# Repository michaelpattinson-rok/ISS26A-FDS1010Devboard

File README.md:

# FDS1010 Devboard E.1

Rev E.1 is an 85 × 60 mm, two layer, through hole Devboard for one FDS1010 channel. Signal Bench 3.7.11 records the board over USB using the original Raspberry Pi Pico W or Arduino UNO R4 Minima.

| Start here | Contents |
| --- | --- |
| [Assembly and use PDF](Assembly%20and%20Use.pdf) | 77 pages covering components, soldering, orientation, wiring, diagnostics, and bench checks. The software pages document the earlier finite capture workflow. |
| [Pico wiring PNG](Pico%20W%20to%20Devboard%20E.1%20Wiring.png) · [Uno wiring PNG](Arduino%20UNO%20R4%20Minima%20to%20Rev%20E.1%20Wiring.png) | Physical pins and power for both supported Signal Bench hosts. |
| [Board and ordering](BOARD.md) | Editable KiCad, fabrication archive, two board DigiKey basket, jumper and probe map, and design checks. |
| [Arduino run data](Data/README.md) | Full Arduino Project archive, run index, and SHA-256 checks. |
| [Firmware](Firmware/README.md) · [macOS app](Software/README.md) | App download, firmware images, operation, and verification. |
| [Mechanical](Mechanical/README.md) | Bare board STEP, assembly geometry, Blender scripts, and three reference views. |

Use one host and a regulated **3.3 V Devboard supply**. Remove power before changing wiring or J4. Connect J1.1 VMID to the FDS1010 anode and J1.2 SUM to its cathode. Keep both detector leads off ground. Start with a known ADC input and Main at 100,000 samples/s, 1×. See the board and firmware guides before power up.

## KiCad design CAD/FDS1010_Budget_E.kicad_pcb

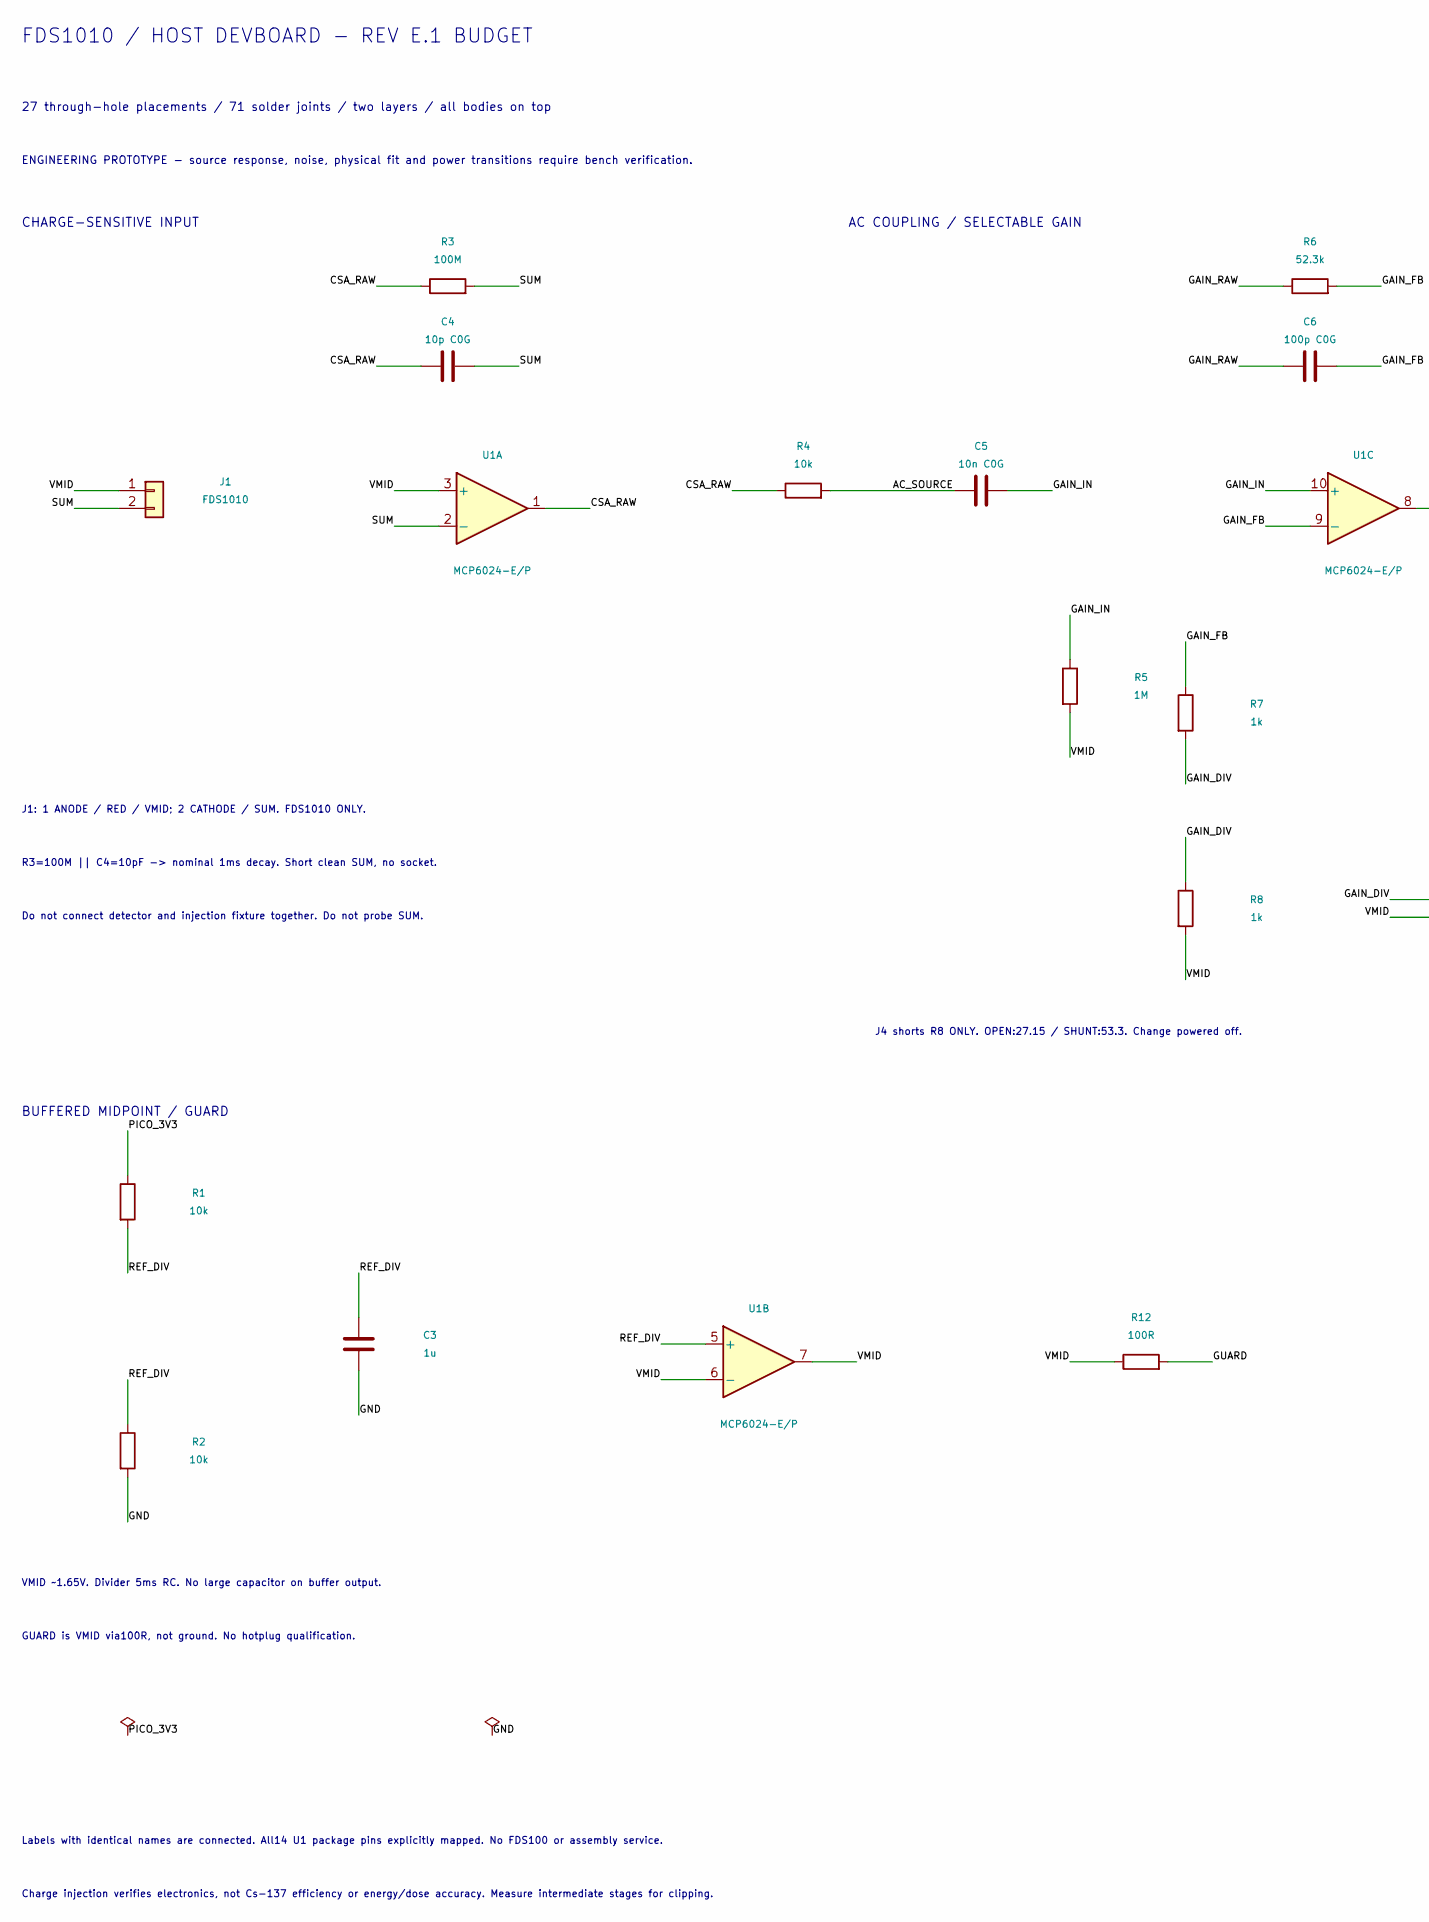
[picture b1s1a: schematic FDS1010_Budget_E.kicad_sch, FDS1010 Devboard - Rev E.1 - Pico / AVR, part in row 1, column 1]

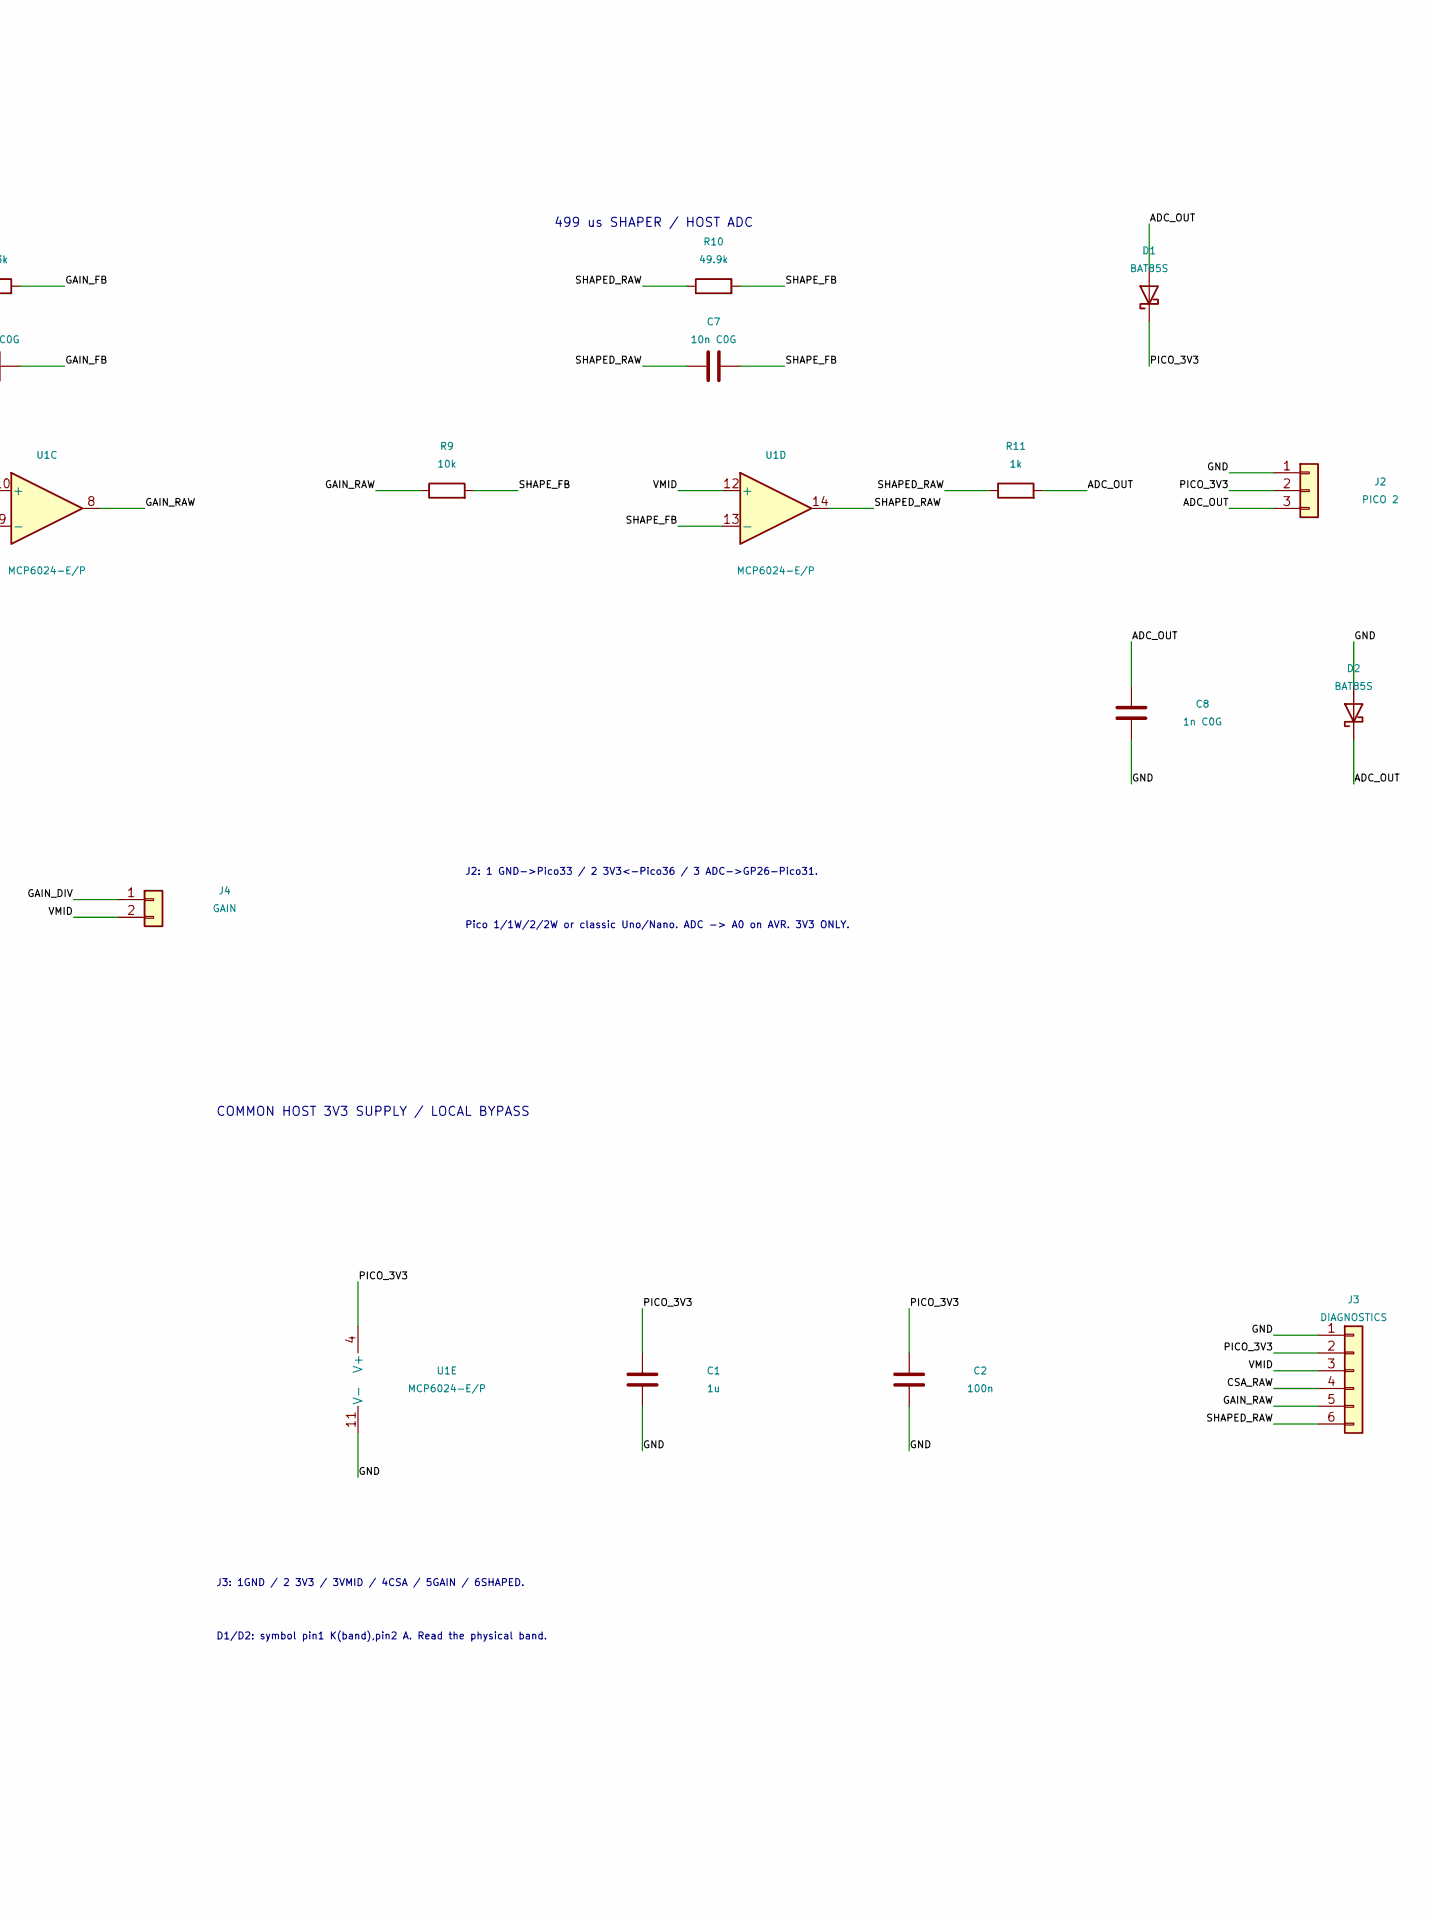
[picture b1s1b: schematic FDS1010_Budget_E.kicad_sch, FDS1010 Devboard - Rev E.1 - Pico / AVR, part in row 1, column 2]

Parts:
C1: 1u; C1; MPN FG28X5R1H105KRT00
C2: 100n; C2; MPN FG18X7R1H104KNT00
C3: 1u; C3; MPN FG28X5R1H105KRT00
C4: 10p C0G; C4; MPN C317C100J1G5TA
C5: 10n C0G; C5; MPN FG24C0G2E103JNT00
C6: 100p C0G; C6; MPN FG28C0G1H101JNT06
C7: 10n C0G; C7; MPN FG24C0G2E103JNT00
C8: 1n C0G; C8; MPN FA18C0G2A102JNU00
D1: BAT85S; D1; MPN BAT85S-TAP
D2: BAT85S; D2; MPN BAT85S-TAP
J1: FDS1010; J1; MPN M20-9990245
J2: PICO 2; J2; MPN M20-9990345
J3: DIAGNOSTICS; J3; MPN M20-9990645
J4: GAIN; J4; MPN M20-9990245
R1: 10k; R1; MPN MFR-25FRF52-10K
R2: 10k; R2; MPN MFR-25FRF52-10K
R3: 100M; R3; MPN MHR0317SA107F70
R4: 10k; R4; MPN MFR-25FRF52-10K
R5: 1M; R5; MPN MFR-25FRF52-1M
R6: 52.3k; R6; MPN MFR-25FBF52-52K3
R7: 1k; R7; MPN RNF14FTD1K00
R8: 1k; R8; MPN RNF14FTD1K00
R9: 10k; R9; MPN MFR-25FRF52-10K
R10: 49.9k; R10; MPN MFR-25FTE52-49K9
R11: 1k; R11; MPN RNF14FTD1K00
R12: 100R; R12; MPN RNF14FTD100R
U1: MCP6024-E/P; U1; MPN MCP6024-E/P

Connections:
/AC_SOURCE: C5.1, R4.2
/ADC_OUT: C8.1, D1.2 (A), D2.1 (K), J2.3, R11.2
/CSA_RAW: C4.1, J3.4, R3.1, R4.1, U1.1
/GAIN_DIV: J4.1, R7.2, R8.1
/GAIN_FB: C6.2, R6.2, R7.1, U1.9 (-)
/GAIN_IN: C5.2, R5.1, U1.10 (+)
/GAIN_RAW: C6.1, J3.5, R6.1, R9.1, U1.8
/GND: C1.2, C2.2, C3.2, C8.2, D2.2 (A), J2.1, J3.1, R2.2, U1.11 (V-)
/GUARD: R12.2
/PICO_3V3: C1.1, C2.1, D1.1 (K), J2.2, J3.2, R1.1, U1.4 (V+)
/REF_DIV: C3.1, R1.2, R2.1, U1.5 (+)
/SHAPED_RAW: C7.1, J3.6, R10.1, R11.1, U1.14
/SHAPE_FB: C7.2, R9.2, R10.2, U1.13 (-)
/SUM: C4.2, J1.2, R3.2, U1.2 (-)
/VMID: J1.1, J3.3, J4.2, R5.2, R8.2, R12.1, U1.3 (+), U1.6 (-), U1.7, U1.12 (+)

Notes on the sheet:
FDS1010 / HOST DEVBOARD - REV E.1 BUDGET
27 through-hole placements / 71 solder joints / two layers / all bodies on top
ENGINEERING PROTOTYPE - source response, noise, physical fit and power transitions require bench verification.
CHARGE-SENSITIVE INPUT
AC COUPLING / SELECTABLE GAIN
499 us SHAPER / HOST ADC
J1: 1 ANODE / RED / VMID; 2 CATHODE / SUM. FDS1010 ONLY.
R3=100M || C4=10pF -> nominal 1ms decay. Short clean SUM, no socket.
Do not connect detector and injection fixture together. Do not probe SUM.
J4 shorts R8 ONLY. OPEN:27.15 / SHUNT:53.3. Change powered off.
J2: 1 GND->Pico33 / 2 3V3<-Pico36 / 3 ADC->GP26-Pico31.
Pico 1/1W/2/2W or classic Uno/Nano. ADC -> A0 on AVR. 3V3 ONLY.
BUFFERED MIDPOINT / GUARD
COMMON HOST 3V3 SUPPLY / LOCAL BYPASS
VMID ~1.65V. Divider 5ms RC. No large capacitor on buffer output.
GUARD is VMID via100R, not ground. No hotplug qualification.
J3: 1GND / 2 3V3 / 3VMID / 4CSA / 5GAIN / 6SHAPED.
D1/D2: symbol pin1 K(band),pin2 A. Read the physical band.
Labels with identical names are connected. All14 U1 package pins explicitly mapped. No FDS100 or assembly service.
Charge injection verifies electronics, not Cs-137 efficiency or energy/dose accuracy. Measure intermediate stages for clipping.

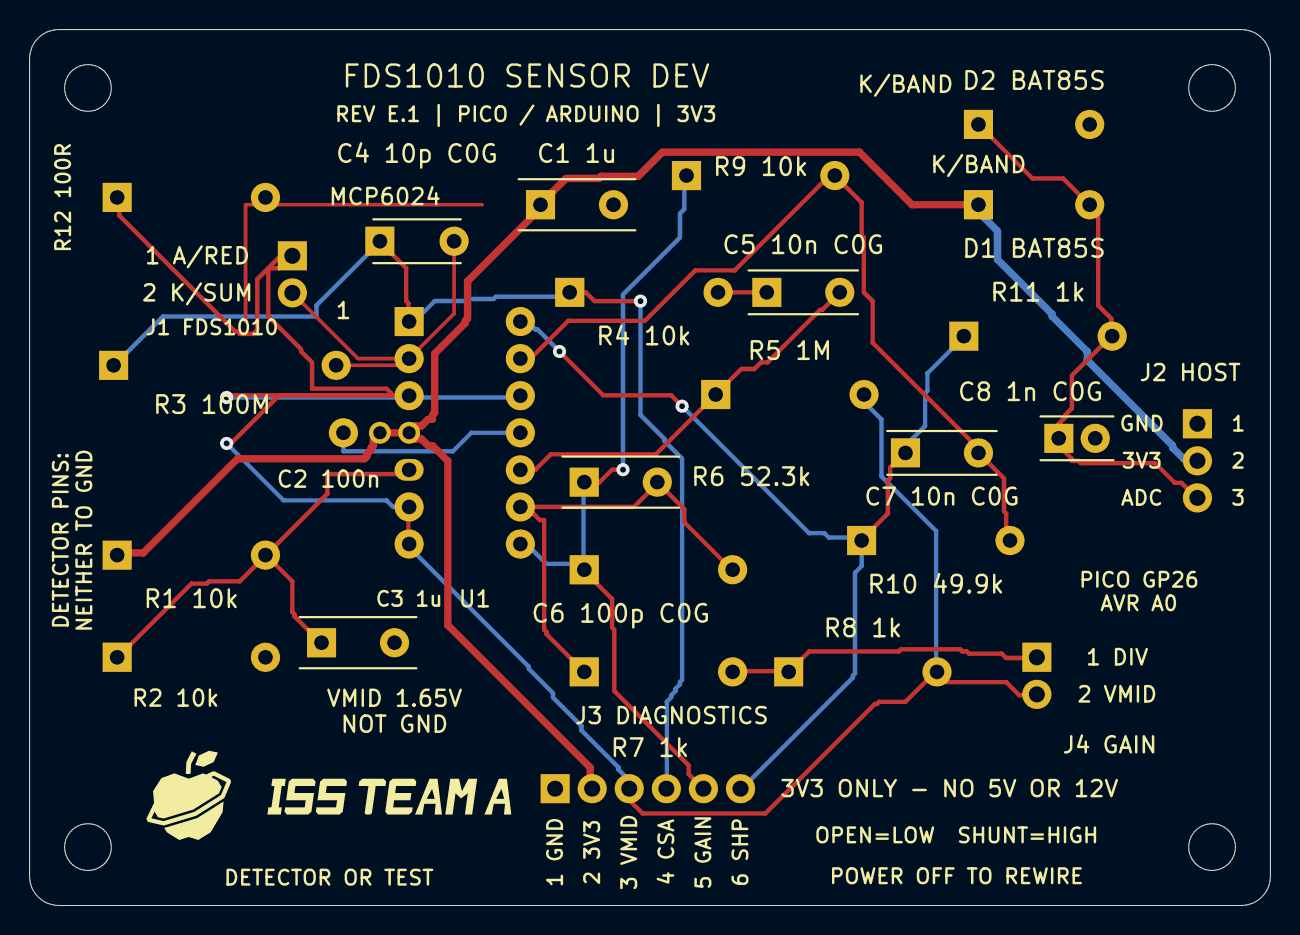
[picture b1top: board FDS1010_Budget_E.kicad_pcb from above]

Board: 2 copper layers, 85.0 x 60.0 mm, 31 parts (0 on the bottom side), 14 nets.

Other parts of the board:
H1, H2, H3, H4: MountingHole_3.2mm_M3
